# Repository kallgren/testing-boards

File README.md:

## Sweep v2.1 Original

## Sweep v2.1 NT

## Sweep v2.1 NT Custom Minimal

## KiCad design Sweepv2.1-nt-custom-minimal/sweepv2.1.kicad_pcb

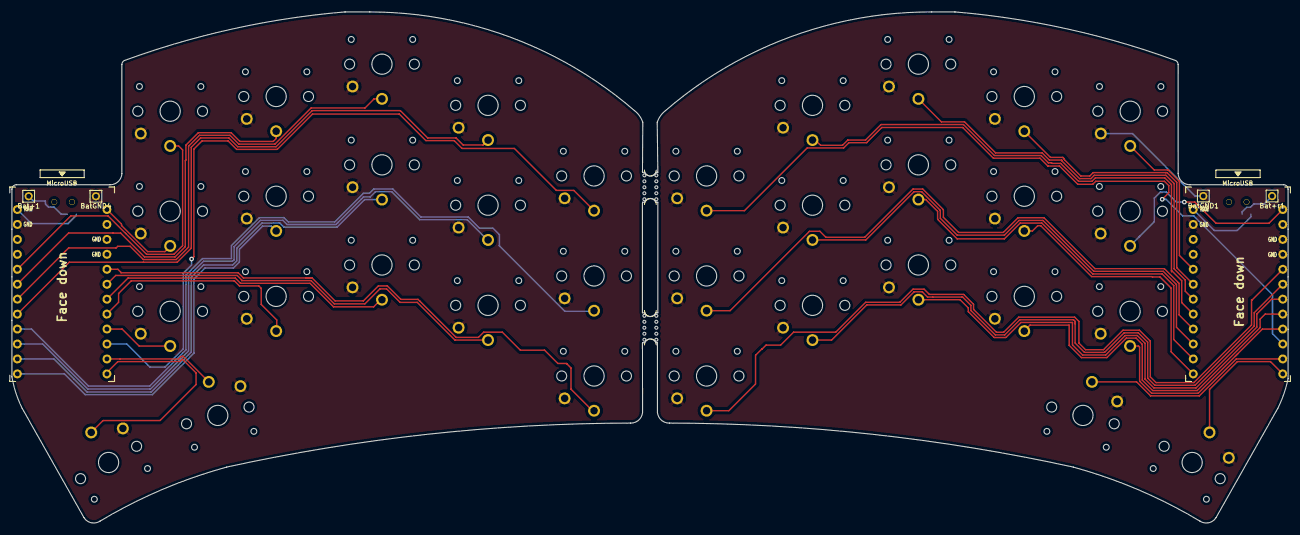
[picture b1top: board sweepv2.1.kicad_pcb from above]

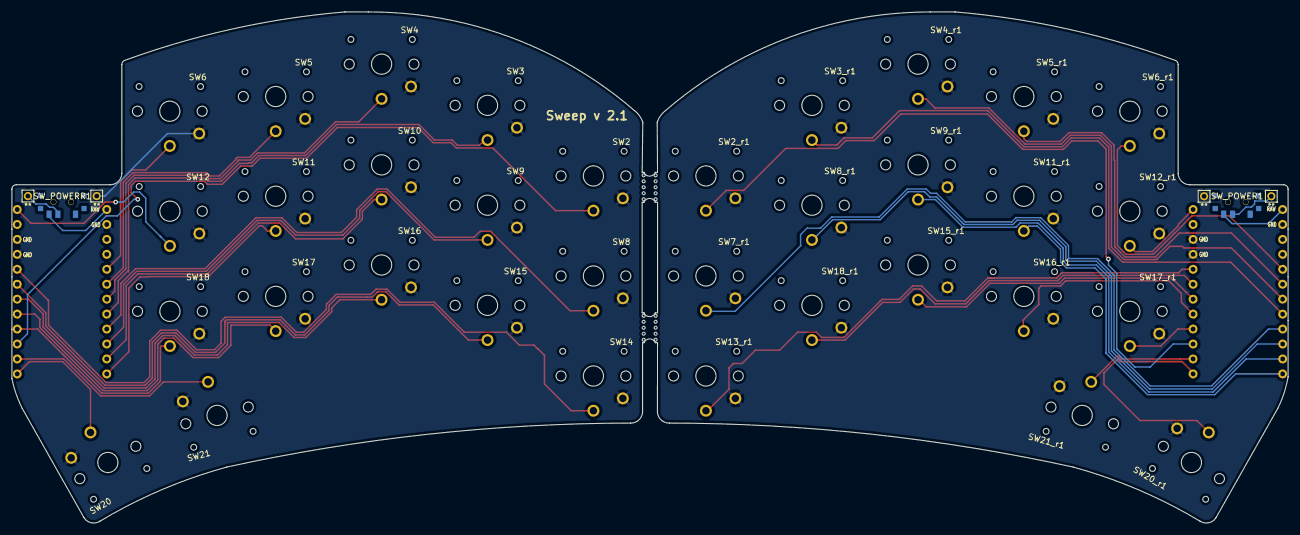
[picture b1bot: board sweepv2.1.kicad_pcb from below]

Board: 2 copper layers, 216.9 x 86.9 mm, 44 parts (2 on the bottom side), 39 nets.

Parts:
Bat+1: MountingHole_Pad; 1pin_conn
Bat+r1: MountingHole_Pad; 1pin_conn
BatGND1, BatGND4: MountingHole_Pad; 1pin_conn
SW2, SW2_r1, SW3, SW3_r1, SW4, SW4_r1, SW5, SW5_r1, SW6, SW6_r1, SW7_r1, SW8, SW8_r1, SW9, SW9_r1, SW10, SW11, SW11_r1, SW12, SW12_r1, SW13_r1, SW14, SW15, SW15_r1, SW16, SW16_r1, SW17, SW17_r1, SW18, SW18_r1, SW20, SW20_r1, SW21, SW21_r1: SW_Push; SW_PG1350_nonrev_DPB
SW_POWER1: SW_SPDT; SPDT_C128955
SW_POWERR1: SW_SPDT; SPDT_C128955
U1, U2: ProMicro-kbd; ProMicro_v3_min
mouse-bite-2mm-slot, mouse-bite-2mm-slot#2: VAL**; mouse-bite-5mm-slot-with-space-for-track

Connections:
BT+: Bat+1.1, SW_POWER1.2
BT+_r: Bat+r1.1, SW_POWERR1.2
Switch1: SW2.1, U1.10
Switch1_r: SW2_r1.1, U2.10
Switch2: SW3.1, U1.17
Switch2_r: SW3_r1.1, U2.17
Switch3: SW4.1, U1.18
Switch3_r: SW4_r1.1, U2.18
Switch4: SW5.1, U1.19
Switch4_r: SW5_r1.1, U2.19
Switch5: SW6.1, U1.20
Switch5_r: SW6_r1.1, U2.20
Switch6: SW8.1, U1.16
Switch6_r: SW7_r1.1, U2.16
Switch7: SW9.1, U1.15
Switch7_r: SW8_r1.1, U2.15
Switch8: SW10.1, U1.14
Switch8_r: SW9_r1.1, U2.14
Switch9: SW11.1, U1.13
Switch9_r: SW11_r1.1, U2.13
Switch10: SW12.1, U1.1
Switch10_r: SW12_r1.1, U2.1
Switch11: SW14.1, U1.5
Switch11_r: SW13_r1.1, U2.5
Switch12: SW15.1, U1.6
Switch12_r: SW18_r1.1, U2.6
Switch13: SW16.1, U1.7
Switch13_r: SW15_r1.1, U2.7
Switch14: SW17.1, U1.8
Switch14_r: SW16_r1.1, U2.8
Switch15: SW18.1, U1.9
Switch15_r: SW17_r1.1, U2.9
Switch16: SW21.1, U1.11
Switch16_r: SW21_r1.1, U2.11
Switch17: SW20.1, U1.12
Switch17_r: SW20_r1.1, U2.12
gnd: BatGND1.1, BatGND4.1, SW2.2, SW2_r1.2, SW3.2, SW3_r1.2, SW4.2, SW4_r1.2, SW5.2, SW5_r1.2, SW6.2, SW6_r1.2, SW7_r1.2, SW8.2, SW8_r1.2, SW9.2, SW9_r1.2, SW10.2, SW11.2, SW11_r1.2, SW12.2, SW12_r1.2, SW13_r1.2, SW14.2, SW15.2, SW15_r1.2, SW16.2, SW16_r1.2, SW17.2, SW17_r1.2, SW18.2, SW18_r1.2, SW20.2, SW20_r1.2, SW21.2, SW21_r1.2, U1.3, U1.4, U1.23, U2.3, U2.4, U2.23
raw: SW_POWER1.3, SW_POWERR1.3, U1.24, U2.24
vcc: U1.21, U2.21

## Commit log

2022-04-01 Add nt custom minimal: no TRRS, reset, crab, puck, text
2022-04-01 nt custom minimal: add gerber_to_order plugin export artifacts
    The gerber_to_order export fixes an issue where holes for the
    microcontrollers and switches would appear offset on Y-axis in JLCPCB's
    gerber viewer. Just to be on the safe side.
2022-04-02 Add readme with screenshots for comparing the versions
2022-04-02 Add DRC report from before the gerber export for future reference
